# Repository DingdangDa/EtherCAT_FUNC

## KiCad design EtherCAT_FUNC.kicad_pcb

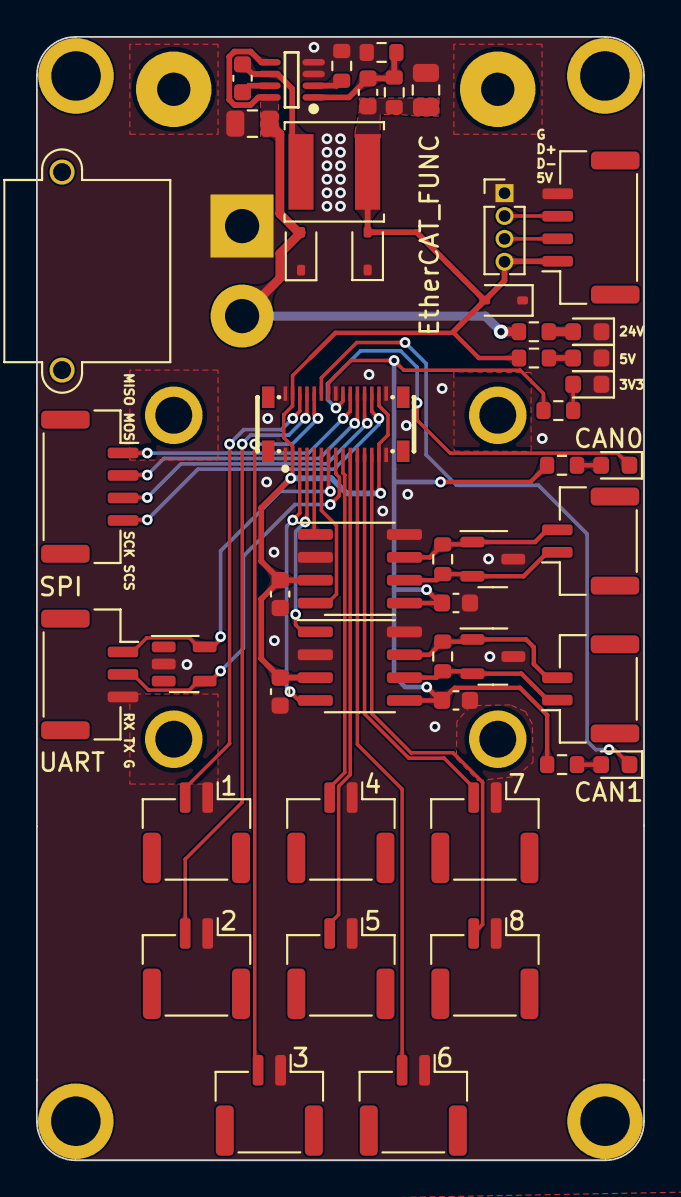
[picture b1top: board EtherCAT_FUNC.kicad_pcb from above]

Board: 2 copper layers, 33.7 x 62.4 mm, 59 parts (0 on the bottom side), 39 nets.

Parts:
C1: 4.7u; C_0805_2012Metric
C2, C3: 10n; C_0603_1608Metric
C4: 22u; C_0805_2012Metric
C5, C6, C7, C8: 100n; C_0603_1608Metric
D1, D2: BLUE; LED_0603_1608Metric
D3: GREEN; LED_0603_1608Metric
D4: YELLOW; LED_0603_1608Metric
D5: RED; LED_0603_1608Metric
D6, D7: BV05C; D_SOD-323
D8: BV24C; D_SOD-323
H1, H2, H3, H10: MountingHole; M1.6
H4, H5, H6, H7: MountingHole; M2_HOLE
H8, H9: MountingHole; M2_noHOLE
J1: axt430124; axt330124
J2, J3: Conn_01x02; JST_GH_SM02B-GHS-TB_1x02-1MP_P1.25mm_Horizontal
J4, J6: Conn_01x04; JST_GH_SM04B-GHS-TB_1x04-1MP_P1.25mm_Horizontal
J5: Conn_01x02; AMASS_XT30PW-M_1x02_P2.50mm_Horizontal
J7: Conn_01x04; PinHeader_1x04_P1.27mm_Vertical
J8: Conn_01x03; JST_GH_SM03B-GHS-TB_1x03-1MP_P1.25mm_Horizontal
J9, J10, J11, J12, J13, J14, J15, J16: Conn_01x02; JST_GH_BM02B-GHS-TBT_1x02-1MP_P1.25mm_Vertical
L1: 22uH; L_Sunlord_SWPA5040S
R1: 100K; R_0603_1608Metric
R2: 150K; R_0603_1608Metric
R3: 20.5K; R_0603_1608Metric
R4, R5, R8, R9: 1K; R_0603_1608Metric
R6, R7: 120; R_0603_1608Metric
R10: 10K; R_0603_1608Metric
U1: SY8303AAIC; SOT-23-8_L3.0-W1.7-P0.65-LS2.8-BR
U2, U3: TJA1051T-3; SOIC-8_3.9x4.9mm_P1.27mm
U4, U5: SOT-23-3
U6: ESDS314; SOT-23-5

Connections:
3V3: C5.1, C6.1, J1.24, R4.2, R5.2, R8.2, U2.5 (VIO), U3.5 (VIO)
+5V: C3.2, C4.2, C7.1, C8.1, D6.2 (A2), D7.2 (A2), J1.2, J1.14, J1.17, J1.29, J6.1, J7.4, L1.2, R2.1, R9.2, U2.3 (VCC), U3.3 (VCC)
+24V: C1.2, D8.2 (A2), J5.2, R10.2, U1.5 (IN), U1.8 (EN)
/CAN/CAN0_H: J2.2, R6.1, U2.7 (CANH), U4.1 (H)
/CAN/CAN0_L: J2.1, R6.2, U2.6 (CANL), U4.2 (L)
/CAN/CAN1_H: J3.2, R7.1, U3.7 (CANH), U5.1 (H)
/CAN/CAN1_L: J3.1, R7.2, U3.6 (CANL), U5.2 (L)
/CAN/FDCAN1_RX: J1.6, U2.4 (RXD)
/CAN/FDCAN1_TX: J1.5, U2.1 (TXD)
/CAN/FDCAN2_RX: J1.3, U3.4 (RXD)
/CAN/FDCAN2_TX: J1.4, U3.1 (TXD)
/GPIO1: J1.28, J9.2
/GPIO2: J1.27, J10.2
/GPIO3: J1.26, J11.2
/GPIO4: J1.9, J12.2
/GPIO5: J1.10, J13.2
/GPIO6: J1.11, J14.2
/GPIO7: J1.12, J15.2
/GPIO8: J1.13, J16.2
/POWER/D+: J6.3, J7.2
/POWER/D-: J6.2, J7.3
/SPI_MISO: J1.21, J4.1
/SPI_MOSI: J1.20, J4.2
/SPI_SCK: J1.19, J4.3
/SPI_SCS: J1.18, J4.4
/UART_RX: J1.7, J8.1, U6.5 (I/O4)
/UART_TX: J1.8, J8.2, U6.4 (I/O3)
GND: C1.1, C4.1, C5.2, C6.2, C7.2, C8.2, D3.1 (K), D4.1 (K), D5.1 (K), D6.1 (A1), D7.1 (A1), D8.1 (A1), J1.1, J1.15, J1.16, J1.23, J1.30, J5.1, J6.4, J7.1, J8.3, J9.1, J10.1, J11.1, J12.1, J13.1, J14.1, J15.1, J16.1, R1.1, R3.1, U1.3 (GND), U1.4 (GND), U2.2 (GND), U2.8 (S), U3.2 (GND), U3.8 (S), U4.3 (GND), U5.3 (GND), U6.2 (GND)
LED_CAN0: D1.1 (K), J1.22
LED_CAN1: D2.1 (K), J1.25
unnamed: D1.2 (A), R4.1
unnamed: D2.2 (A), R5.1
unnamed: D3.2 (A), R8.1
unnamed: D4.2 (A), R9.1
unnamed: D5.2 (A), R10.1
unnamed: C2.1, U1.7 (BS)
unnamed: C3.1, R2.2, R3.2, U1.1 (FB)
unnamed: R1.2, U1.2 (FS)
unnamed: C2.2, L1.1, U1.6 (LX)

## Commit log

2023-06-28 Change conns of GPIO
2023-06-29 Change footprints of M2 and axt330124
2023-07-08 All 0603 version
2023-07-14 Official version
2023-07-19 Fixed layout_GND bug
